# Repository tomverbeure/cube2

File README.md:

Cube2
=====

# Build Instructions

*Verilog generation*

The cube uses a Colorlight 5A-75B HUB75 controller board, revision v6.1. It has
an ECP5-25 FPGA that's running a custom bitstream.

The RTL for that bitstream can be found in the `./rtl` directory. It's written
with the SpinalHDL framework.

# RISC-V Toolchain

On Ubuntu, I did:

```sh
git clone https://github.com/riscv/riscv-gnu-toolchain
cd riscv-gnu-toolchain
./configure --prefix="/opt/riscv-multi --enable-multilib
make -j $(nproc)
```

This compiles a RISC-V compile that supports all possible configurations, including
RV32. You can check the configurations with:

```sh
opt/riscv-multi/bin/riscv64-unknown-elf-gcc --print-multi-lib
```
```
.;
rv32i/ilp32;@march=rv32i@mabi=ilp32
rv32im/ilp32;@march=rv32im@mabi=ilp32
rv32iac/ilp32;@march=rv32iac@mabi=ilp32
rv32imac/ilp32;@march=rv32imac@mabi=ilp32
rv32imafc/ilp32f;@march=rv32imafc@mabi=ilp32f
rv64imac/lp64;@march=rv64imac@mabi=lp64
rv64imafdc/lp64d;@march=rv64imafdc@mabi=lp64d
```

Total area is ~2GB.

# macOS

```
brew install openfpgaloader
```

```
tomverbeure@Toms-Air 5a-75b % /opt/homebrew/bin/openFPGALoader --scan-usb
found 3 USB device
Bus device vid:pid       probe type      manufacturer serial               product
000 003    0x0403:0x6014 ft232H          Digilent     210251A08870         Digilent USB Device
```

```
tomverbeure@Toms-Air 5a-75b % /opt/homebrew/bin/openFPGALoader -v --vid 0x0403 --pid 0x6014 --detect
No cable or board specified: using direct ft2232 interface
Cable VID overridden
Cable PID overridden
Jtag frequency : requested 6.00MHz   -> real 6.00MHz
found 1 devices
index 0:
	idcode 0x1111043
	manufacturer lattice
	family ECP5
	model  LFE5UM-25
	irlength 8
```

# SpinalHDL

See https://spinalhdl.github.io/SpinalDoc-RTD/master/SpinalHDL/Getting%20Started/Install%20and%20setup.html#mac-os-x-installation

# Build prjtrellis

```
git clone --recursive git@github.com:YosysHQ/prjtrellis.git
cd prjtrellis/libtrellis
cmake -DCMAKE_INSTALL_PREFIX=/opt/prjtrellis .
make -j$(nproc)
sudo make install
```

# Build nextpnr

```
git clone git@github.com:YosysHQ/nextpnr.git
cd nextpnr
mkdir build
cd build
cmake .. -DARCH=ecp5 -DTRELLIS_INSTALL_PREFIX=/opt/prjtrellis -DCMAKE_INSTALL_PREFIX=/opt/nextpnr
make -j$(nproc)
```

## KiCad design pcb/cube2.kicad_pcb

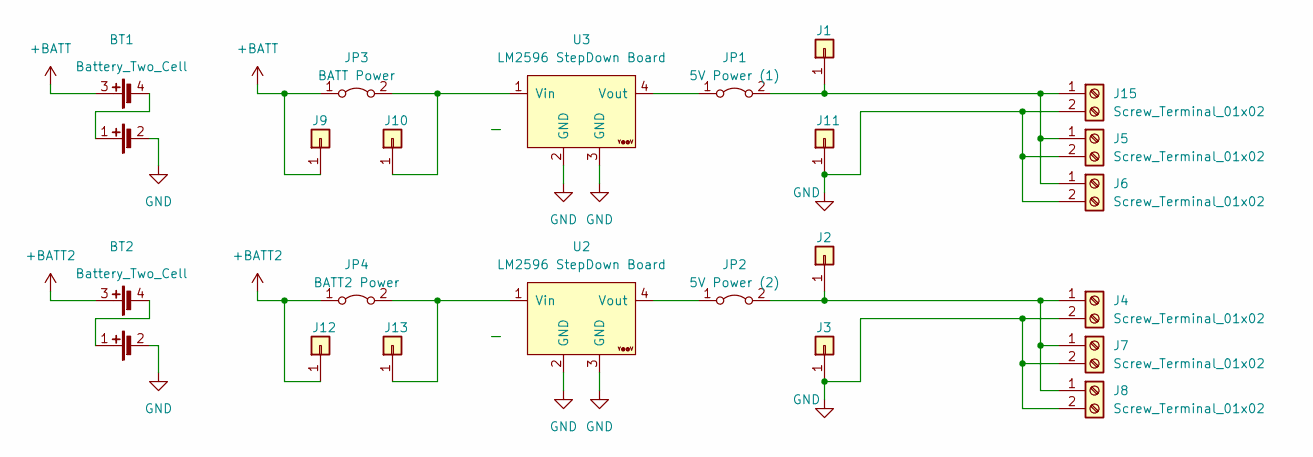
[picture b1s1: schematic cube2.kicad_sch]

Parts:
BT1, BT2: Battery_Two_Cell; battery_holder
J1, J2, J3, J9, J10, J11, J12, J13: Conn_01x01; TestPoint_Loop_D3.80mm_Drill2.0mm
J4, J5, J6, J7, J8, J15: Screw_Terminal_01x02; TerminalBlock_MAX-MX127-5.0-02P
JP1: 5V Power (1); PinHeader_1x02_P2.54mm_Vertical
JP2: 5V Power (2); PinHeader_1x02_P2.54mm_Vertical
JP3: BATT Power; PinHeader_1x02_P2.54mm_Vertical
JP4: BATT2 Power; PinHeader_1x02_P2.54mm_Vertical
U2, U3: LM2596 StepDown Board; YAAJ_DCDC_StepDown_LM2596

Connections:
+BATT: BT1.3 (+), J9.1, JP3.1 (A)
+BATT2: BT2.3 (+), J12.1, JP4.1 (A)
GND: BT1.2 (-), BT2.2 (-), J3.1, J4.2, J5.2, J6.2, J7.2, J8.2, J11.1, J15.2, U2.2 (GND), U2.3 (GND), U3.2 (GND), U3.3 (GND)
unnamed: BT1.1 (+), BT1.4 (-)
unnamed: BT2.1 (+), BT2.4 (-)
unnamed: J1.1, J5.1, J6.1, J15.1, JP1.2 (B)
unnamed: J2.1, J4.1, J7.1, J8.1, JP2.2 (B)
unnamed: J10.1, JP3.2 (B), U3.1 (Vin)
unnamed: J13.1, JP4.2 (B), U2.1 (Vin)
unnamed: JP1.1 (A), U3.4 (Vout)
unnamed: JP2.1 (A), U2.4 (Vout)

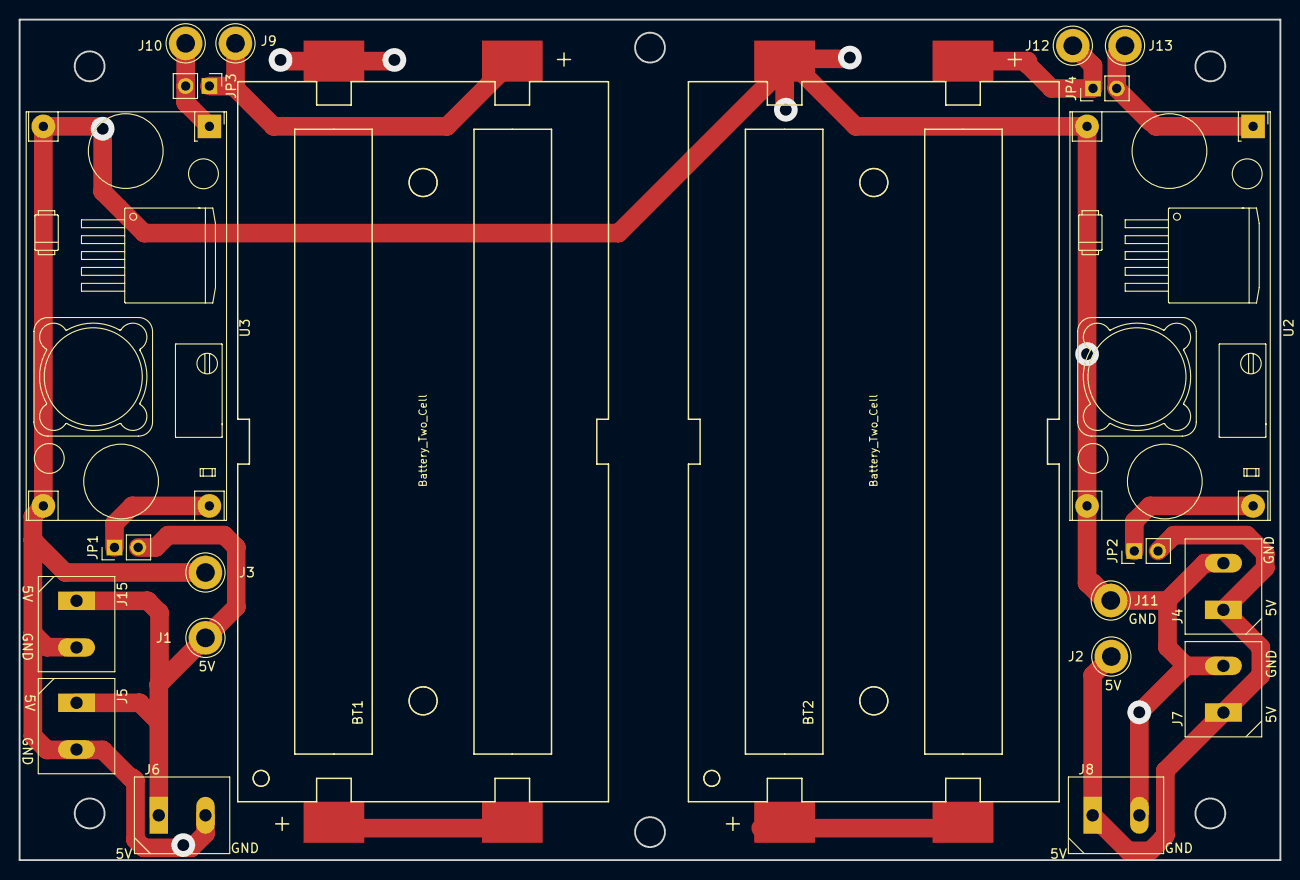
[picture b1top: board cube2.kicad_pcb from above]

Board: 2 copper layers, 135.0 x 90.0 mm, 22 parts (0 on the bottom side), 11 nets.

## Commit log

2023-08-16 WIP.
2023-10-09 Cube2 power PCB
2023-10-17 Add drill files to gerbers.
2023-11-03 Connect to FPGA.
2023-11-03 Working blinky.
2023-11-03 Add .gitignore
2023-11-03 Empty SpinalHDL template
2023-11-03 Rename to Cube2 project.
2023-11-03 Use 25->50MHz PLL.
2023-11-04 Checkpoint. Hub75 instances compile.
2023-11-04 Hub75StreamLight verison works.
2023-11-04 Synthesis & PnR scripts.
2023-11-04 Add bitstream flash command.
2023-11-04 Ignore svf
2023-11-04 Programmable number of HUB75 channels.
2023-11-04 Make channels generic.
2023-11-04 Refactor bit vector interface into Hub75PhyFeed bundle.
2023-11-05 Apply Hub75StreamerLight changes to Hub75Streamer.
2023-11-05 Hub75Streamer + VexRiscv + sw compiles
2023-11-05 Testbench. Increment col_cntr. Basic bringup.
2023-11-05 CPU can somewhat control the screen.
2023-11-05 Uniform address space for LED memories.
2023-11-05 Pixel addressing is correct.
2023-11-06 Add double buffering.
2023-11-06 Rick dancing with a bit less corruption.
2023-11-08 Render Rick pixels at double resolution.
2023-11-10 Reduce output FIFO. Fix corruption issue.
2023-11-10 Add gamma and dimming in SW.
2023-11-11 Assign panel locations.
2023-11-11 Adjust panel rotation for uniform coordinates.
2023-11-12 Pacman running around the cube.
2023-11-12 Pacman map.
2023-11-12 Refactor SW.
2023-11-13 Rendering dots + walls. WIP.
2023-11-13 Patch bitstream with new SW contents.
2023-11-13 Map is looking good.
2023-11-13 Align bitmaps.
2024-03-07 Save FreeCAD changes. (Unknown.)
2024-04-07 Build instructions.
2024-11-01 Add active grid.
2024-11-01 Don't loop in pacman_render().
2024-11-01 Pacman eats dots.
2024-11-01 Pacman looks in the right direction.
2024-11-02 Ghosts are following the maze.
2024-11-02 Replenish dots.
2024-11-02 Multi-phase ghosts.
2024-11-02 Ghosts get scared when eating big dot.
2024-11-02 Ghosts can be eaten.
2024-11-03 Pacman wilts before dying.
2024-11-03 Respawn faster.
2024-11-03 Add license.
2024-11-03 Add generated Verilog netlist.
2024-11-07 Print LedMem configuration.
2024-11-07 Enable 6 LED panels. Correctly calculate clock for desired refresh rate.
2024-11-07 LedMem: debug mode outputs constant color on all panels.
2024-11-10 Ring rendering for negative Y coords.
2024-11-11 Expand grid above in preparation of top rendering
2024-11-11 Render top field.
2024-12-30 Changes to make compile with regular gcc.
2024-12-30 MARCH/MABI defines.
2024-12-30 Add link to locally compiled Ubuntu risc-v toolchain
2024-12-30 RISC-V build instructions.
2024-12-31 Run on PC with empty HW shims.
